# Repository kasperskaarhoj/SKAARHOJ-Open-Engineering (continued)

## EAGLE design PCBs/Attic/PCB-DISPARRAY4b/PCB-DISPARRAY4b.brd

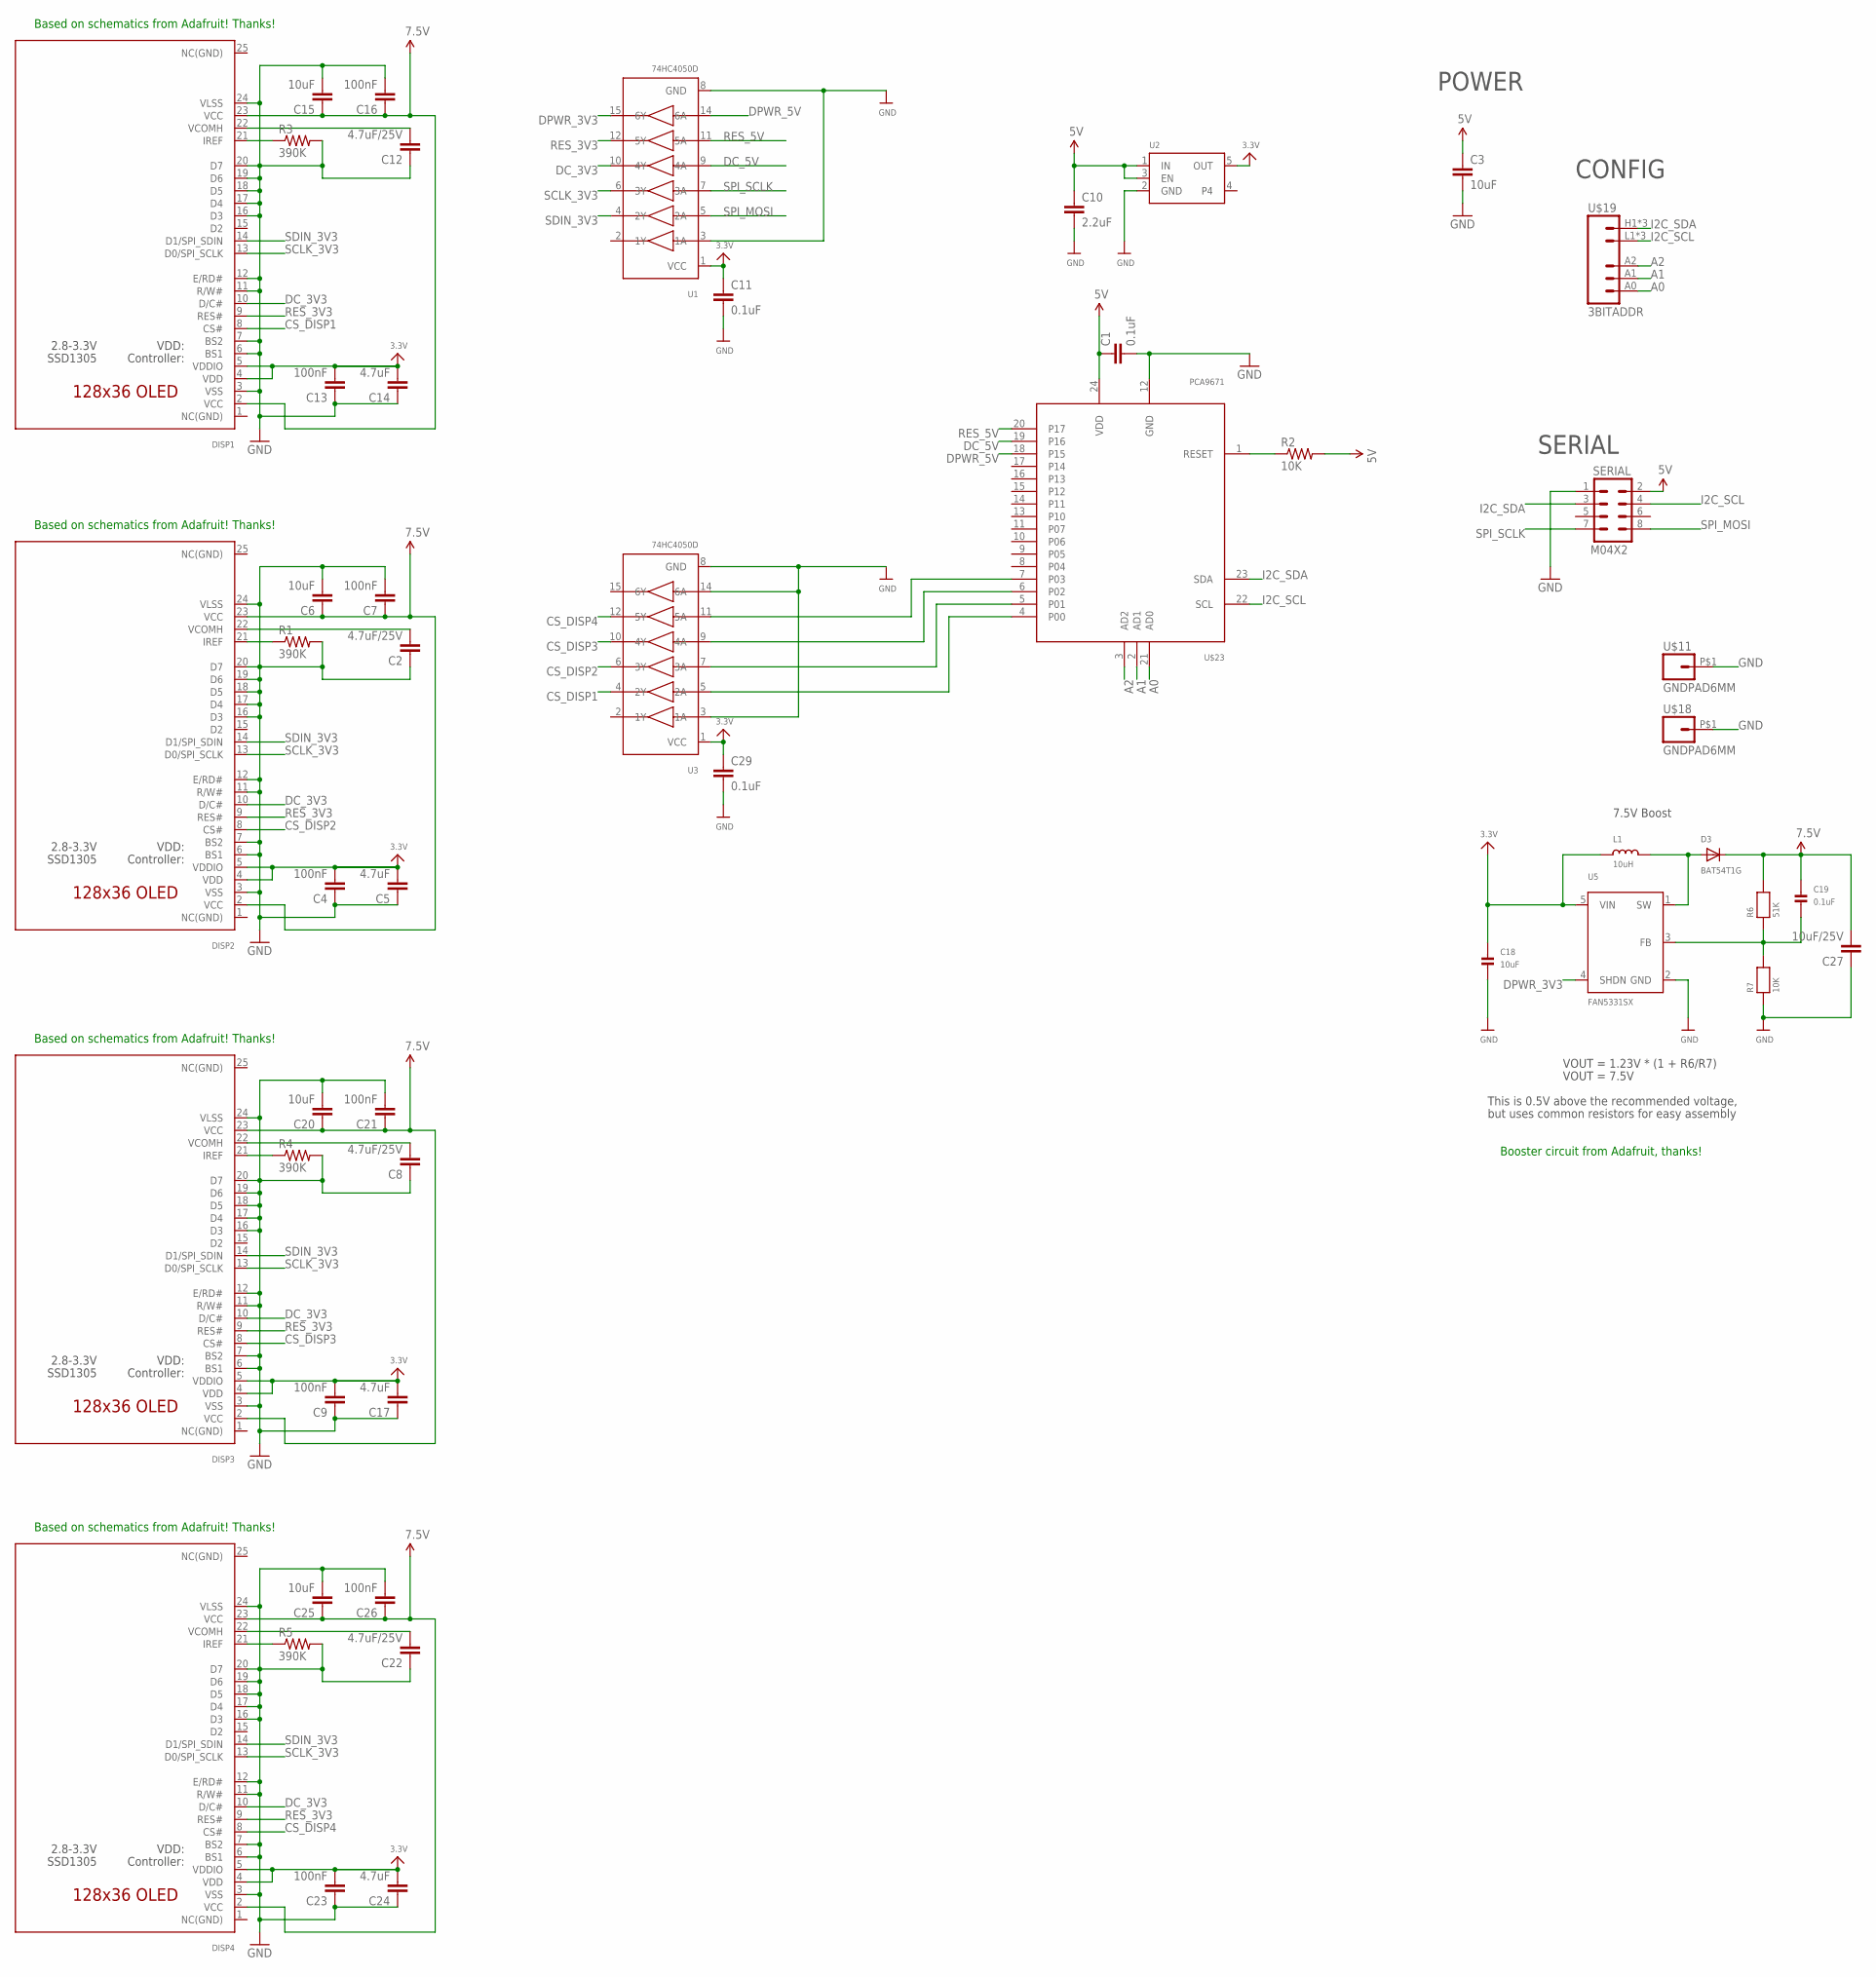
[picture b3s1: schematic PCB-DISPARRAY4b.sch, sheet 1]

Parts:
C1, C11, C29: 0.1uF; 0603-CAP
C2, C8, C12, C22: 4.7uF/25V; 0805
C3, C6, C15, C18, C20, C25: 10uF; 0805
C4, C7, C9, C13, C16, C21, C23, C26: 100nF; 0603-CAP
C5, C14, C17, C24: 4.7uF; 0603-CAP
C10: 2.2uF; 0603-CAP
C19: 0.1uF; 0603
C27: 10uF/25V; 0805
D3: BAT54T1G; SOD-123
DISP1, DISP2, DISP3, DISP4: ER-OLED011-1TOP; ER-OLED011-1
L1: 10uH; INDUCTOR_1007
R1, R3, R4, R5: 390K; 0603-RES
R2: 10K; 0603-RES
R6: 51K; 0603
R7: 10K; 0603
SERIAL: M04X2; 2X4
U1, U3: 74HC4050D; TSSOP16
U2: VREG_SOT23-5; SOT23-5
U5: FAN5331SX; SOT23-5
U$11, U$18: GNDPAD6MM; 3.2MMPAD6MM
U$19: 3BITADDR
U$23: PCA9671; TSSOP24

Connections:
3.3V: C4.2, C5.2, C9.2, C11.1, C13.2, C14.2, C17.2, C18.1, C23.2, C24.2, C29.1, DISP1.4 (VDD), DISP1.5 (VDDIO), DISP2.4 (VDD), DISP2.5 (VDDIO), DISP3.4 (VDD), DISP3.5 (VDDIO), DISP4.4 (VDD), DISP4.5 (VDDIO), L1.P$1 (1), U1.1 (VCC), U2.5 (OUT), U3.1 (VCC), U5.5 (VIN)
5V: C1.1, C3.1, C10.1, R2.2, SERIAL.2, U2.1 (IN), U2.3 (EN), U$23.24 (VDD)
7.5V: C6.1, C7.1, C15.1, C16.1, C19.1, C20.1, C21.1, C25.1, C26.1, C27.2, D3.C, DISP1.2 (VCC), DISP1.23 (VCC), DISP2.2 (VCC), DISP2.23 (VCC), DISP3.2 (VCC), DISP3.23 (VCC), DISP4.2 (VCC), DISP4.23 (VCC), R6.2
A0: U$19.A0, U$23.21 (AD0)
A1: U$19.A1, U$23.2 (AD1)
A2: U$19.A2, U$23.3 (AD2)
CS_DISP1: DISP1.8 (CS#), U3.4 (2Y)
CS_DISP2: DISP2.8 (CS#), U3.6 (3Y)
CS_DISP3: DISP3.8 (CS#), U3.10 (4Y)
CS_DISP4: DISP4.8 (CS#), U3.12 (5Y)
DC_3V3: DISP1.10 (D/C#), DISP2.10 (D/C#), DISP3.10 (D/C#), DISP4.10 (D/C#), U1.10 (4Y)
DC_5V: U1.9 (4A), U$23.19 (P16)
DPWR_3V3: U1.15 (6Y), U5.4 (SHDN)
DPWR_5V: U1.14 (6A), U$23.18 (P15)
GND: C1.2, C2.1, C3.2, C4.1, C5.1, C6.2, C7.2, C8.1, C9.1, C10.2, C11.2, C12.1, C13.1, C14.1, C15.2, C16.2, C17.1, C18.2, C20.2, C21.2, C22.1, C23.1, C24.1, C25.2, C26.2, C27.1, C29.2, DISP1.3 (VSS), DISP1.6 (BS1), DISP1.7 (BS2), DISP1.11 (R/W#), DISP1.12 (E/RD#), DISP1.16 (D3), DISP1.17 (D4), DISP1.18 (D5), DISP1.19 (D6), DISP1.20 (D7), DISP1.24 (VLSS), DISP2.3 (VSS), DISP2.6 (BS1), DISP2.7 (BS2), DISP2.11 (R/W#), DISP2.12 (E/RD#), DISP2.16 (D3), DISP2.17 (D4), DISP2.18 (D5), DISP2.19 (D6), DISP2.20 (D7), DISP2.24 (VLSS), DISP3.3 (VSS), DISP3.6 (BS1), DISP3.7 (BS2), DISP3.11 (R/W#), DISP3.12 (E/RD#), DISP3.16 (D3), DISP3.17 (D4), DISP3.18 (D5), DISP3.19 (D6), DISP3.20 (D7), DISP3.24 (VLSS), DISP4.3 (VSS), DISP4.6 (BS1), DISP4.7 (BS2), DISP4.11 (R/W#), DISP4.12 (E/RD#), DISP4.16 (D3), DISP4.17 (D4), DISP4.18 (D5), DISP4.19 (D6), DISP4.20 (D7), DISP4.24 (VLSS), R1.2, R3.2, R4.2, R5.2, R7.1, SERIAL.1, U1.3 (1A), U1.8 (GND), U2.2 (GND), U3.3 (1A), U3.8 (GND), U3.14 (6A), U5.2 (GND), U$11.P$1, U$18.P$1, U$23.12 (GND)
I2C_SCL: SERIAL.4, U$19.L1 (GND), U$19.L2 (GND), U$19.L3 (GND), U$23.22 (SCL)
I2C_SDA: SERIAL.3, U$19.H1 (VCC), U$19.H2 (VCC), U$19.H3 (VCC), U$23.23 (SDA)
unnamed: R2.1, U$23.1 (RESET)
unnamed: DISP2.21 (IREF), R1.1
unnamed: C2.2, DISP2.22 (VCOMH)
unnamed: DISP3.21 (IREF), R4.1
unnamed: DISP1.21 (IREF), R3.1
unnamed: C8.2, DISP3.22 (VCOMH)
unnamed: DISP4.21 (IREF), R5.1
unnamed: C22.2, DISP4.22 (VCOMH)
unnamed: C12.2, DISP1.22 (VCOMH)
unnamed: D3.A, L1.P$2 (2), U5.1 (SW)
unnamed: C19.2, R6.1, R7.2, U5.3 (FB)
unnamed: U3.5 (2A), U$23.4 (P00)
unnamed: U3.7 (3A), U$23.5 (P01)
unnamed: U3.9 (4A), U$23.6 (P02)
unnamed: U3.11 (5A), U$23.7 (P03)
RES_3V3: DISP1.9 (RES#), DISP2.9 (RES#), DISP3.9 (RES#), DISP4.9 (RES#), U1.12 (5Y)
RES_5V: U1.11 (5A), U$23.20 (P17)
SCLK_3V3: DISP1.13 (D0/SPI_SCLK), DISP2.13 (D0/SPI_SCLK), DISP3.13 (D0/SPI_SCLK), DISP4.13 (D0/SPI_SCLK), U1.6 (3Y)
SDIN_3V3: DISP1.14 (D1/SPI_SDIN), DISP2.14 (D1/SPI_SDIN), DISP3.14 (D1/SPI_SDIN), DISP4.14 (D1/SPI_SDIN), U1.4 (2Y)
SPI_MOSI: SERIAL.8, U1.5 (2A)
SPI_SCLK: SERIAL.7, U1.7 (3A)

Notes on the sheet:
SERIAL
POWER
CONFIG
Based on schematics from Adafruit! Thanks!
VOUT = 1.23V * (1 + R6/R7)
VOUT = 7.5V
This is 0.5V above the recommended voltage,
but uses common resistors for easy assembly
7.5V Boost
Booster circuit from Adafruit, thanks!

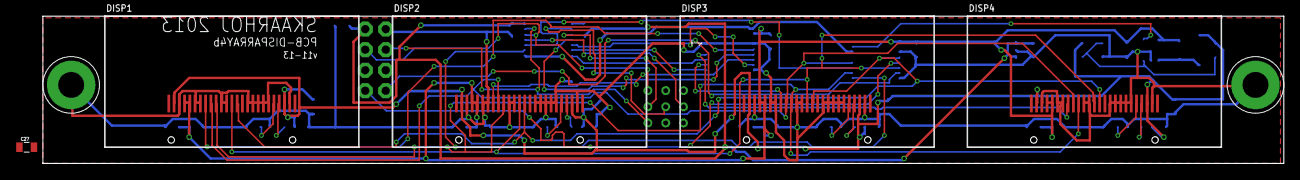
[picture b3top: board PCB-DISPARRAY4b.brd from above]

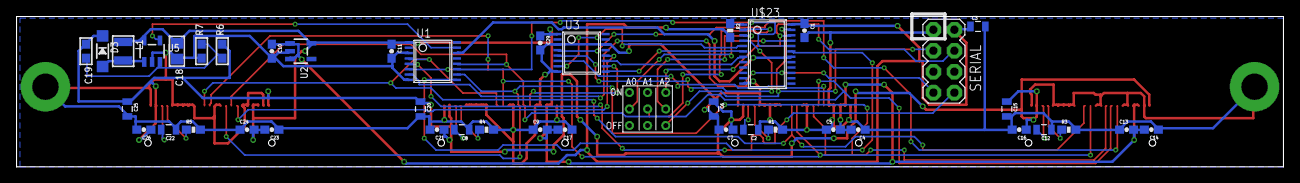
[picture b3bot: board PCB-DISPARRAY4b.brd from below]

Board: 2 copper layers, 153.4 x 18.2 mm, 50 parts (43 on the bottom side), 38 nets.

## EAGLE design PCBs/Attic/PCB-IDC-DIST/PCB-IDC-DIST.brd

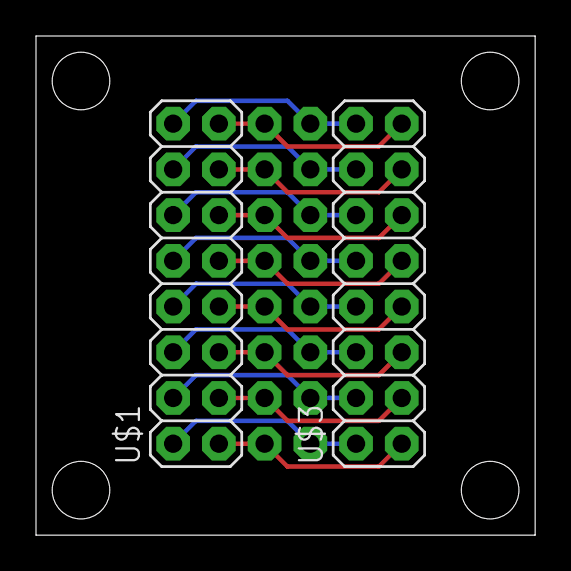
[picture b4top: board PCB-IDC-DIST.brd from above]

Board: 2 copper layers, 27.7 x 27.7 mm, 3 parts (1 on the bottom side), 16 nets.

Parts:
U$1, U$2, U$3: M08X2; 2X8

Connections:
unnamed: U$1.2, U$2.2, U$3.2
unnamed: U$1.4, U$2.4, U$3.4
unnamed: U$1.6, U$2.6, U$3.6
unnamed: U$1.8, U$2.8, U$3.8
unnamed: U$1.10, U$2.10, U$3.10
unnamed: U$1.12, U$2.12, U$3.12
unnamed: U$1.14, U$2.14, U$3.14
unnamed: U$1.16, U$2.16, U$3.16
unnamed: U$1.1, U$2.1, U$3.1
unnamed: U$1.3, U$2.3, U$3.3
unnamed: U$1.5, U$2.5, U$3.5
unnamed: U$1.7, U$2.7, U$3.7
unnamed: U$1.9, U$2.9, U$3.9
unnamed: U$1.11, U$2.11, U$3.11
unnamed: U$1.13, U$2.13, U$3.13
unnamed: U$1.15, U$2.15, U$3.15

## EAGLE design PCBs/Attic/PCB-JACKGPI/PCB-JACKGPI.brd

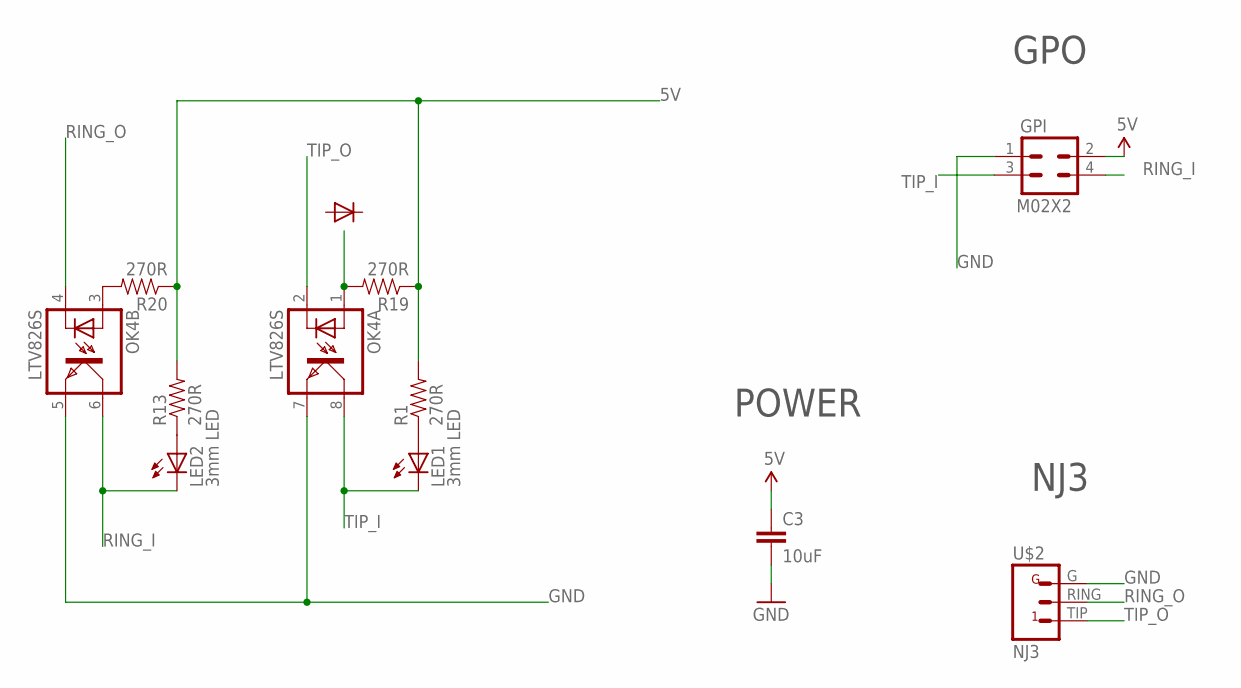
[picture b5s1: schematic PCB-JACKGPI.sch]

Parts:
C3: 10uF; 0805
GPI: M02X2; 2X2
LED1, LED2: 3mm LED; LED3MM
OK4: LTV826S; DIL8-SMD
R1, R13, R19, R20: 270R; 0603-RES
U$2: NJ3; NJ3FP6C

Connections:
5V: C3.1, GPI.2, R1.2, R13.2, R19.1, R20.1
GND: C3.2, GPI.1, OK4.5 (EMIT), OK4.7 (EMIT), U$2.G
unnamed: LED1.A, R1.1
unnamed: LED2.A, R13.1
unnamed: OK4.1 (A), R19.2
unnamed: OK4.3 (A), R20.2
RING_I: GPI.4, LED2.K (C), OK4.6 (COL)
RING_O: OK4.4 (C), U$2.RING (2)
TIP_I: GPI.3, LED1.K (C), OK4.8 (COL)
TIP_O: OK4.2 (C), U$2.TIP (1)

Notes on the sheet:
NJ3
GPO
POWER

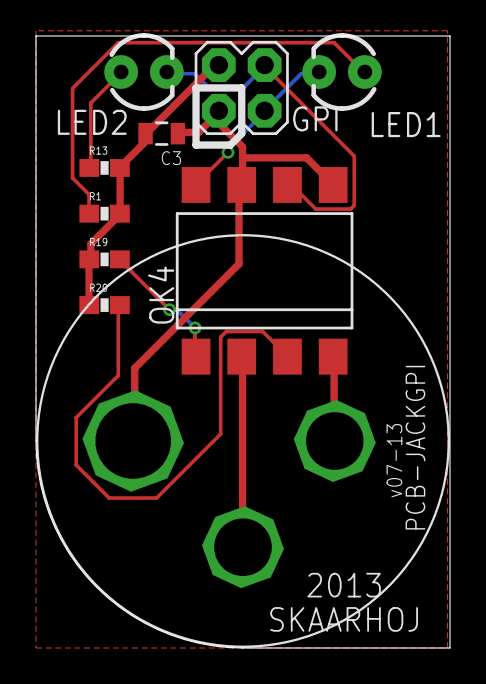
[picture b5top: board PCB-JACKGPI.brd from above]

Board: 2 copper layers, 23.0 x 34.0 mm, 10 parts (0 on the bottom side), 10 nets.

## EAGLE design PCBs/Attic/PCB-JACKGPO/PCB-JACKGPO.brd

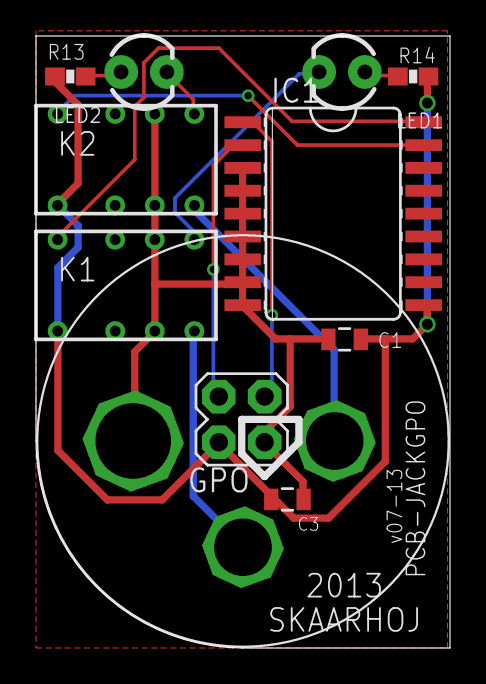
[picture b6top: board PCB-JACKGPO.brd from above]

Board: 2 copper layers, 23.0 x 34.0 mm, 11 parts (0 on the bottom side), 12 nets.

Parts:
C1: 100nF; 0805
C3: 10uF; 0805
GPO: M02X2; 2X2
IC1: ULN2803A; SO18W
K1, K2: RELAY5VIM03; DS2Y
LED1, LED2: 3mm LED; LED3MM
R13, R14: 270R; 0603-RES
U$2: NJ3; NJ3FP6C

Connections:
5V: C1.2, C3.1, GPO.2, IC1.10, K1.1, K2.1, R13.2, R14.2
GND: C1.1, C3.2, GPO.1, IC1.3, IC1.4, IC1.5, IC1.6, IC1.7, IC1.8, IC1.9, K1.P1, K1.P2, K2.P1, K2.P2, U$2.G
unnamed: K1.S2, LED1.K
unnamed: IC1.18, K1.16
unnamed: K2.S2, LED2.K
unnamed: IC1.17, K2.16
unnamed: LED2.A, R13.1
unnamed: LED1.A, R14.1
RING_I: GPO.4, IC1.2
RING_O: K2.S1, U$2.RING
TIP_I: GPO.3, IC1.1
TIP_O: K1.S1, U$2.TIP

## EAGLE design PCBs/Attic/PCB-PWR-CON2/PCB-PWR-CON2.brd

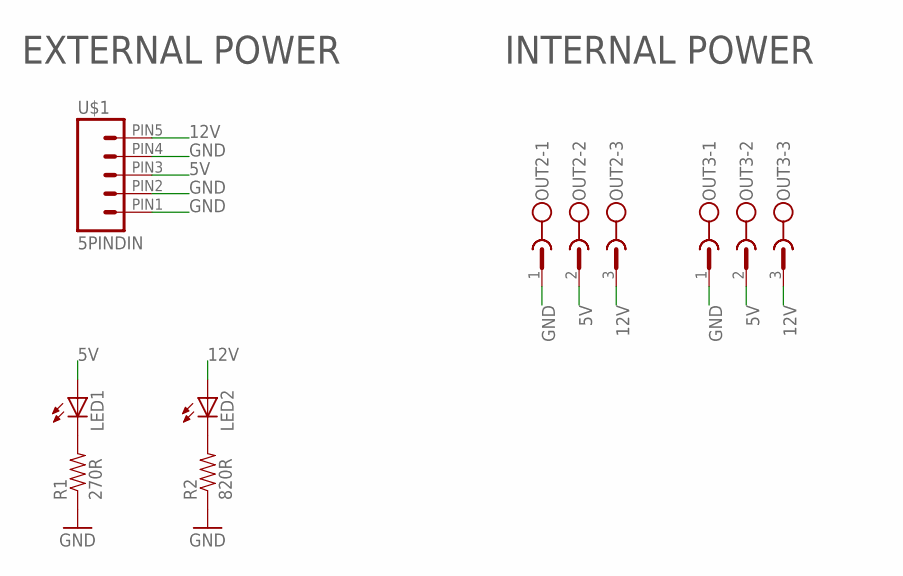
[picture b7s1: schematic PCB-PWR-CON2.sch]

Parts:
LED1, LED2: LED3MM
OUT2, OUT3: CON1; MSTBV3
R1: 270R; 0603-RES
R2: 820R; 0603-RES
U$1: 5PINDIN

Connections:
5V: LED1.A, OUT2.2, OUT3.2, U$1.PIN3 (3)
12V: LED2.A, OUT2.3, OUT3.3, U$1.PIN5 (5)
GND: OUT2.1, OUT3.1, R1.1, R2.1, U$1.PIN1 (1), U$1.PIN2 (2), U$1.PIN4 (4)
unnamed: LED1.K (C), R1.2
unnamed: LED2.K (C), R2.2

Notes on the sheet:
INTERNAL POWER
EXTERNAL POWER

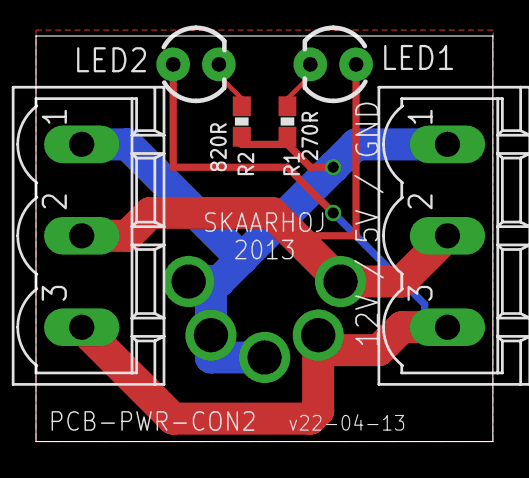
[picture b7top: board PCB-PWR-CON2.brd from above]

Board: 2 copper layers, 25.4 x 22.5 mm, 7 parts (0 on the bottom side), 5 nets.
